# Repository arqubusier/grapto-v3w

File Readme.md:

# Prerequisites

## CAD Development

- Install Freecad
- Install KiCad
- Install Freecad KiCad StepUp plugin.
- install ergogen https://docs.ergogen.xyz/ (see below)
- Install https://github.com/perigoso/keyswitch-kicad-library.
  - Use the "Plugin and Content Manager" program of Kicad.
  - add the library path for Switch_Keyboard_Kailh 
  - Add value of the Kicad variable "KICAD6_3DMODEL_DIR" to secondary 3D folder location in KiCad StepUp
- Download the usb connector 3d model from https://www.molex.com/molex/part/partModels.jsp?&prodLevel=part&partNo=2169900001&channel=products
  to <repo>/grapto-v3w-pcb/216990-0001_stp/
  
### ergogen

$ npm i ergogen
installing globally causes permission errors depending on environment

You need to hack the footprints in gen_src/footprints into your local install of ergogen.

run ergogen (-d flag ouputs svg in addition to svg)

$ cd gen_src
$ ergogen -d config.yaml

Then copy kicad pcbs into the respective kicad project

## FW Development

  # src
  git clone git@github.com:arqubusier/zmk.git

  # packages
  sudo pacman -S git \
    autoconf \
    automake \
    ccache \
    dfu-util \
    libtool \
    make \
    gcc \
    ninja \
    cmake \

  pip install --user west

  # toolchains
  export ZSDK_VERSION=0.13.2
wget -q "https://github.com/zephyrproject-rtos/sdk-ng/releases/download/v${ZSDK_VERSION}/zephyr-toolchain-arm-${ZSDK_VERSION}-linux-x86_64-setup.run" && \
    sh "zephyr-toolchain-arm-${ZSDK_VERSION}-linux-x86_64-setup.run" --quiet -- -d ~/.local/zephyr-sdk-${ZSDK_VERSION} && \
    rm "zephyr-toolchain-arm-${ZSDK_VERSION}-linux-x86_64-setup.run"

  # west setup
  cd <zmk-repo>
  west init -l app/
  west update
  west zephyr-export
  pip install --user -r zephyr/scripts/requirements-base.txt

  yay -S nrf5x-command-line-tools
# FW Development

## Flashing

cd <zmk-repo>
cd app
west flash 
cd 
# FW Development

## Building

west build -p -b grapto_v3w

## Flashing

west flash

# Usage

## Pair on Arch Linux

Set report mode characteristic to report

$ sudo bluetoothctl
menu scan
clean
transport le
back
scan on
connect E9:9E:30:E3:E4:5B

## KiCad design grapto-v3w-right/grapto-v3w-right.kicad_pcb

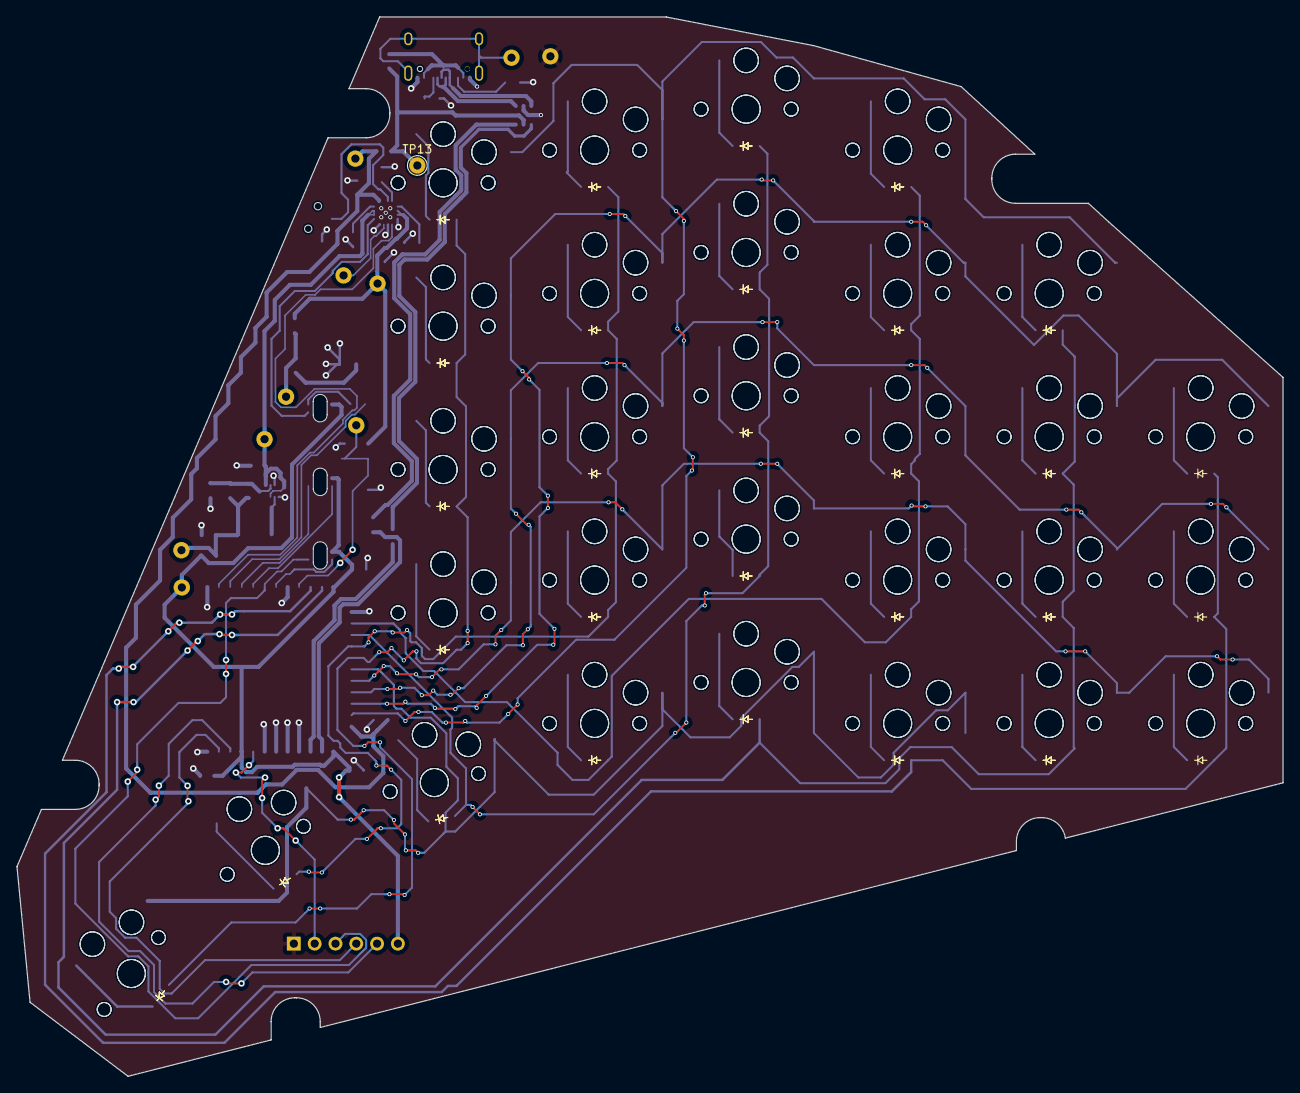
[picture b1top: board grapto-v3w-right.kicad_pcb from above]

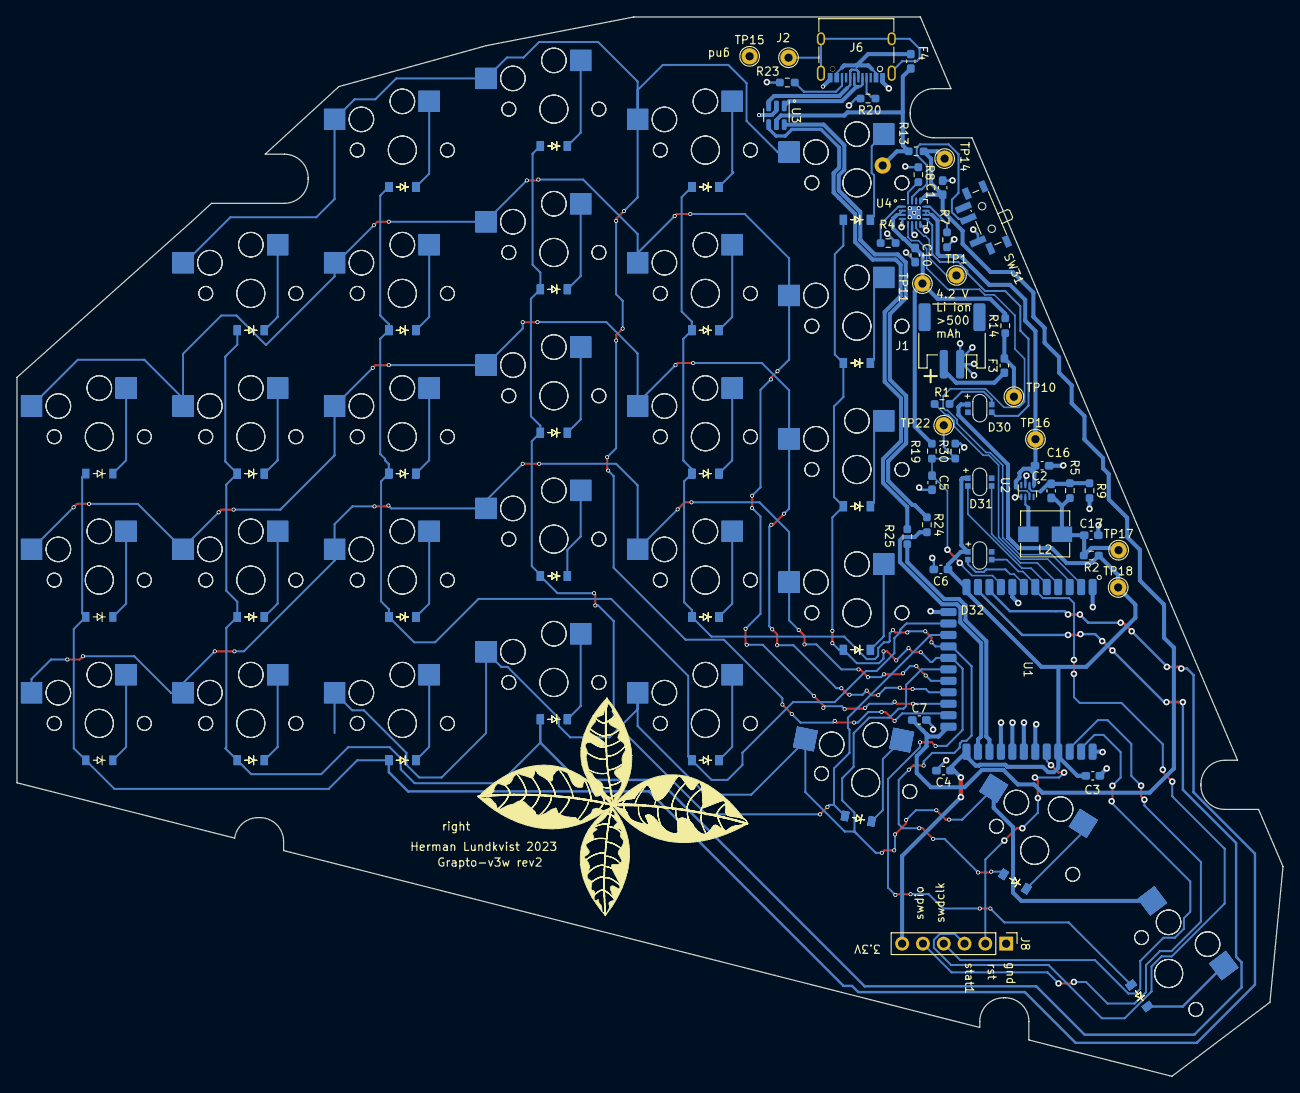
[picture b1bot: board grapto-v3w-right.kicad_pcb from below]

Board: 2 copper layers, 154.6 x 129.3 mm, 163 parts (49 on the bottom side), 78 nets.

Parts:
C1: 1u; C_0603_1608Metric_Pad1.08x0.95mm_HandSolder
C2: 120p; C_0603_1608Metric_Pad1.08x0.95mm_HandSolder
C3, C4, C6, C7, C10, C16, C17: 22u; C_0603_1608Metric_Pad1.08x0.95mm_HandSolder
C5: .1u; C_0603_1608Metric_Pad1.08x0.95mm_HandSolder
D30, D31, D32: LED_ARGB; 23-23B-R6GHBHC-A01-2A
D33, D34, D35, D36, D37, D38, D39, D40, D41, D42, D43, D44, D45, D46, D47, D48, D49, D50, D51, D52, D53, D54, D55, D56, D57, D58, D59, D60, D61, D62, D63, D64, D65, D66, D67, D68, D69, D70, D71, D72, D73, D74, D75, D76, D77, D78, D79, D80, D81, D82, D83, D84, D85, D86, D87: ComboDiode
F3, F4: Polyfuse; Fuse_0603_1608Metric_Pad1.05x0.95mm_HandSolder
J1: Conn_01x02_Female; JST_PH_S2B-PH-SM4-TB_1x02-1MP_P2.00mm_Horizontal
J2: Conn_01x01_Female; TestPoint_THTPad_D2.0mm_Drill1.0mm
J6: USB_C_Receptacle_USB2.0; USB_C_Receptacle_G-Switch_GT-USB-7004
J8: Conn_01x06_Male; PinHeader_1x06_P2.54mm_Vertical
L2: 470n; MHCI05020-R47M-R8
R1: 68; R_0603_1608Metric_Pad0.98x0.95mm_HandSolder
R2, R13, R14: 0.01m; R_0603_1608Metric_Pad0.98x0.95mm_HandSolder
R4: 10K; R_0603_1608Metric_Pad0.98x0.95mm_HandSolder
R5: 453k; R_0603_1608Metric_Pad0.98x0.95mm_HandSolder
R7: 3.3K; R_0603_1608Metric_Pad0.98x0.95mm_HandSolder
R8: 2.2K; R_0603_1608Metric_Pad0.98x0.95mm_HandSolder
R9: 100k; R_0603_1608Metric_Pad0.98x0.95mm_HandSolder
R19: 1M2; R_0603_1608Metric_Pad0.98x0.95mm_HandSolder
R20, R23: 5.1k; R_0603_1608Metric_Pad0.98x0.95mm_HandSolder
R24, R25: 22; R_0603_1608Metric_Pad0.98x0.95mm_HandSolder
R30: 3M; R_0603_1608Metric_Pad0.98x0.95mm_HandSolder
S30, S31, S32, S33, S34, S35, S36, S37, S38, S39, S40, S41, S42, S43, S44, S45, S46, S47, S48, S49, S50, S51, S52, S53, S54, S55, S56, S57, S58, S59, S60, S61, S62, S63, S64, S65, S66, S67, S68, S69, S70, S71, S72, S73, S74, S75, S76, S77, S78, S79, S80, S81, S82, S83, S84, S85, S86, S87: PG1350
SW31: SW_SPDT; SW_SK-3296S-01-L2
TP1, TP10, TP11, TP13, TP14, TP15, TP16, TP17, TP18: TestPoint; TestPoint_THTPad_D2.0mm_Drill1.0mm
TP22: TestPoint_THTPad_D2.0mm_Drill1.0mm
U1: ACN52840
U2: TPS62822DLC; Texas_VSON-HR-8_1.5x2mm_P0.5mm
U3: USBLC6-2SC6; SOT-23-6
U4: BQ24075RGT; VQFN-16-1EP_3x3mm_P0.5mm_EP1.6x1.6mm

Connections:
/controller/BatteryManagement/bat+: F3.1, J1.2
/controller/BatteryManagement/bat_fused: C10.1, R14.2, R19.1, TP11.1, U4.2 (BAT), U4.3 (BAT)
/controller/bat_lvl1: D31.3 (GK), U1.4 (P1.15)
/controller/bat_lvl2: D31.4 (BK), U1.5 (P0.02/AIN0)
/controller/chassi: J2.1, J6.S1 (SHIELD)
/controller/chg_led: D30.3 (GK), U4.9 (~CHG)
/controller/fast_chg: U1.2 (P1.10), U4.5 (EN2)
/controller/fast_chg_led: R1.1, U1.3 (P1.13)
/controller/low_batt: C5.1, R19.2, R30.1, TP22.1, U1.9 (P0.31/AIN7)
/controller/reset: J8.2, U1.31 (RST/SWO)
/controller/status1: D32.3 (GK), J8.3, U1.6 (P0.04/AIN1)
/controller/status2: D32.4 (BK), U1.7 (P0.28/AIN4)
/controller/swdclk: J8.4, U1.34 (SWDCLK)
/controller/swdio: J8.5, U1.33 (SWDIO)
/controller/vdd: C3.1, C4.1, C6.1, D30.1 (A), D31.1 (A), D32.1 (A), J8.6, R2.2, TP18.1, U1.12 (VDD), U1.24 (VDD), U1.32 (VDD)
/controller/vusb: C1.1, C7.1, R13.2, TP14.1, U1.23 (VBUS), U4.13 (IN)
unnamed: C2.1, C17.1, L2.2, R2.1, R5.1, TP17.1
unnamed: D30.2 (RK), R1.2
unnamed: F3.2, R14.1, TP10.1
unnamed: SW31.2 (B), U4.15 (SYSOFF)
unnamed: C2.2, R5.2, R9.1, U2.2 (FB)
unnamed: L2.1, U2.6 (SW)
unnamed: R7.1, U4.12 (ILIM)
unnamed: R8.1, U4.16 (ISET)
unnamed: R4.1, U4.1 (TS)
unnamed: TP1.1, U4.7 (~PGOOD)
USB0_N: R24.1, U3.6 (I/O1)
USB0_P: R25.1, U3.4 (I/O2)
USB_N: R24.2, U1.25 (USB_D-)
USB_P: R25.2, U1.26 (USB_D+)
cc1: J6.A5 (CC1), R20.1
cc2: J6.B5 (CC2), R23.1
col0: D52.2, D53.2, D54.2, D55.2, D58.2, D81.2, D82.2, D83.2, D84.2, D87.2, U1.17 (P0.06)
col0row0: D55.1, D84.1, S55.1, S84.1
col0row1: D54.1, D83.1, S54.1, S83.1
col0row2: D53.1, D82.1, S53.1, S82.1
col0row3: D52.1, D81.1, S52.1, S81.1
col0row4: D58.1, D87.1, S58.1, S87.1
col1: D48.2, D49.2, D50.2, D51.2, D57.2, D77.2, D78.2, D79.2, D80.2, D86.2, U1.16 (P0.27)
col1row0: D51.1, D80.1, S51.1, S80.1
col1row1: D50.1, D79.1, S50.1, S79.1
col1row2: D49.1, D78.1, S49.1, S78.1
col1row3: D48.1, D77.1, S48.1, S77.1
col1row4: D57.1, D86.1, S57.1, S86.1
col2: D43.2, D44.2, D45.2, D46.2, D56.2, D72.2, D73.2, D74.2, D75.2, D85.2, U1.15 (P0.26)
col2row0: D46.1, D75.1, S46.1, S75.1
col2row1: D45.1, D74.1, S45.1, S74.1
col2row2: D44.1, D73.1, S44.1, S73.1
col2row3: D43.1, D72.1, S43.1, S72.1
col2row4: D56.1, D85.1, S56.1, S85.1
col3: D38.2, D39.2, D40.2, D41.2, D47.2, D67.2, D68.2, D69.2, D70.2, D76.2, U1.14 (P0.04/AIN2)
col3row0: D41.1, D70.1, S41.1, S70.1
col3row1: D40.1, D69.1, S40.1, S69.1
col3row2: D39.1, D68.1, S39.1, S68.1
col3row3: D38.1, D67.1, S38.1, S67.1
col3row4: D47.1, D76.1, S47.1, S76.1
col4: D33.2, D34.2, D35.2, D36.2, D42.2, D62.2, D63.2, D64.2, D65.2, D71.2, U1.11 (AIN3)
col4row0: D36.1, D65.1, S36.1, S65.1
col4row1: D35.1, D64.1, S35.1, S64.1
col4row2: D34.1, D63.1, S34.1, S63.1
col4row3: D33.1, D62.1, S33.1, S62.1
col4row4: D42.1, D71.1, S42.1, S71.1
col5: D37.2, D59.2, D60.2, D61.2, D66.2, U1.10 (P0.30/AIN6)
col5row1: D61.1, S32.1, S61.1
col5row2: D60.1, S31.1, S60.1
col5row3: D59.1, S30.1, S59.1
col5row4: D37.1, D66.1, S37.1, S66.1
row0: S36.2, S41.2, S46.2, S51.2, S55.2, S65.2, S70.2, S75.2, S80.2, S84.2, U1.22 (P0.12)
row1: S32.2, S35.2, S40.2, S45.2, S50.2, S54.2, S61.2, S64.2, S69.2, S74.2, S79.2, S83.2, U1.21 (P1.09)
row2: S31.2, S34.2, S39.2, S44.2, S49.2, S53.2, S60.2, S63.2, S68.2, S73.2, S78.2, S82.2, U1.20 (P0.08)
row3: S30.2, S33.2, S38.2, S43.2, S48.2, S52.2, S59.2, S62.2, S67.2, S72.2, S77.2, S81.2, U1.19 (P0.09/NFC1)
row4: S37.2, S42.2, S47.2, S56.2, S57.2, S58.2, S66.2, S71.2, S76.2, S85.2, S86.2, S87.2, U1.18 (P0.10/NFC2)
sysgnd: C1.2, C3.2, C4.2, C5.2, C6.2, C7.2, C10.2, C16.2, C17.2, J1.1, J6.A1 (GND), J6.A12 (GND), J6.B1 (GND), J6.B12 (GND), J8.1, R4.2, R7.2, R8.2, R9.2, R20.2, R23.2, R30.2, SW31.1 (A), TP15.1, U1.1 (GND), U1.8 (P0.29/AIN5), U1.13 (GND), U1.27 (P0.13), U1.28 (P0.15), U1.29 (P0.17), U1.30 (P0.24), U1.35 (GND), U2.3 (AGND), U2.5 (PGND), U3.2 (GND), U4.4 (~CE), U4.6 (EN1), U4.8 (VSS), U4.17 (VSS)
usb1_n: J6.A7 (D-), J6.B7 (D-), U3.1 (I/O1)
usb1_p: J6.A6 (D+), J6.B6 (D+), U3.3 (I/O2)
vbus_fused: F4.2, R13.1, TP13.1, U3.5 (VBUS)
vbus_no_fuse: F4.1, J6.A4 (VBUS), J6.A9 (VBUS), J6.B4 (VBUS), J6.B9 (VBUS)
vsys: C16.1, TP16.1, U2.1 (EN), U2.7 (VIN), U4.10 (OUT), U4.11 (OUT)

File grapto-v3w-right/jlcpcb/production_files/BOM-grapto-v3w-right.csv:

Comment,Designator,Footprint,LCSC
1M2,R19,R_0603_1608Metric_Pad0.98x0.95mm_HandSolder,C137774
.1u,C5,C_0603_1608Metric_Pad1.08x0.95mm_HandSolder,C14663
1u,C1,C_0603_1608Metric_Pad1.08x0.95mm_HandSolder,C15849
0.01m,"R13,R14,R2",R_0603_1608Metric_Pad0.98x0.95mm_HandSolder,C21189
3.3K,R7,R_0603_1608Metric_Pad0.98x0.95mm_HandSolder,C22978
3M,R30,R_0603_1608Metric_Pad0.98x0.95mm_HandSolder,C23156
5.1k,"R20,R23",R_0603_1608Metric_Pad0.98x0.95mm_HandSolder,C23186
22,"R24,R25",R_0603_1608Metric_Pad0.98x0.95mm_HandSolder,C23345
100k,R9,R_0603_1608Metric_Pad0.98x0.95mm_HandSolder,C25803
10K,R4,R_0603_1608Metric_Pad0.98x0.95mm_HandSolder,C25804
453k,R5,R_0603_1608Metric_Pad0.98x0.95mm_HandSolder,C273765
68,R1,R_0603_1608Metric_Pad0.98x0.95mm_HandSolder,C27592
LED_ARGB,"D30,D31,D32",23-23B-R6GHBHC-A01-2A,C2827866
Polyfuse,"F3,F4",Fuse_0603_1608Metric_Pad1.05x0.95mm_HandSolder,C2844463
470n,L2,MHCI05020-R47M-R8,C285730
Conn_01x02_Female,J1,JST_PH_S2B-PH-SM4-TB_1x02-1MP_P2.00mm_Horizontal,C295747
2.2K,R8,R_0603_1608Metric_Pad0.98x0.95mm_HandSolder,C4190
TPS62822DLC,U2,Texas_VSON-HR-8_1.5x2mm_P0.5mm,C473385
SW_SPDT,SW31,SW_SK-3296S-01-L2,C500051
,"S59,S60,S61,S62,S63,S64,S65,S66,S67,S68,S69,S70,S71,S72,S73,S74,S75,S76,S77,S78,S79,S80,S81,S82,S83,S84,S85,S86,S87",PG1350,C5333465
BQ24075RGT,U4,VQFN-16-1EP_3x3mm_P0.5mm_EP1.6x1.6mm,C544783
22u,"C10,C16,C17,C3,C4,C6,C7",C_0603_1608Metric_Pad1.08x0.95mm_HandSolder,C59461
USBLC6-2SC6,U3,SOT-23-6,C7519
,"D59,D60,D61,D62,D63,D64,D65,D66,D67,D68,D69,D70,D71,D72,D73,D74,D75,D76,D77,D78,D79,D80,D81,D82,D83,D84,D85,D86,D87",ComboDiode,C81598
120p,C2,C_0603_1608Metric_Pad1.08x0.95mm_HandSolder,C85974
~,TP22,TestPoint_THTPad_D2.0mm_Drill1.0mm,
TestPoint,TP18,TestPoint_THTPad_D2.0mm_Drill1.0mm,
TestPoint,TP17,TestPoint_THTPad_D2.0mm_Drill1.0mm,
TestPoint,TP16,TestPoint_THTPad_D2.0mm_Drill1.0mm,
TestPoint,TP15,TestPoint_THTPad_D2.0mm_Drill1.0mm,
TestPoint,TP14,TestPoint_THTPad_D2.0mm_Drill1.0mm,
TestPoint,TP13,TestPoint_THTPad_D2.0mm_Drill1.0mm,
TestPoint,TP11,TestPoint_THTPad_D2.0mm_Drill1.0mm,
TestPoint,TP10,TestPoint_THTPad_D2.0mm_Drill1.0mm,
TestPoint,TP1,TestPoint_THTPad_D2.0mm_Drill1.0mm,
ACN52840,U1,ACN52840,
USB_C_Receptacle_USB2.0,J6,USB_C_Receptacle_G-Switch_GT-USB-7004,

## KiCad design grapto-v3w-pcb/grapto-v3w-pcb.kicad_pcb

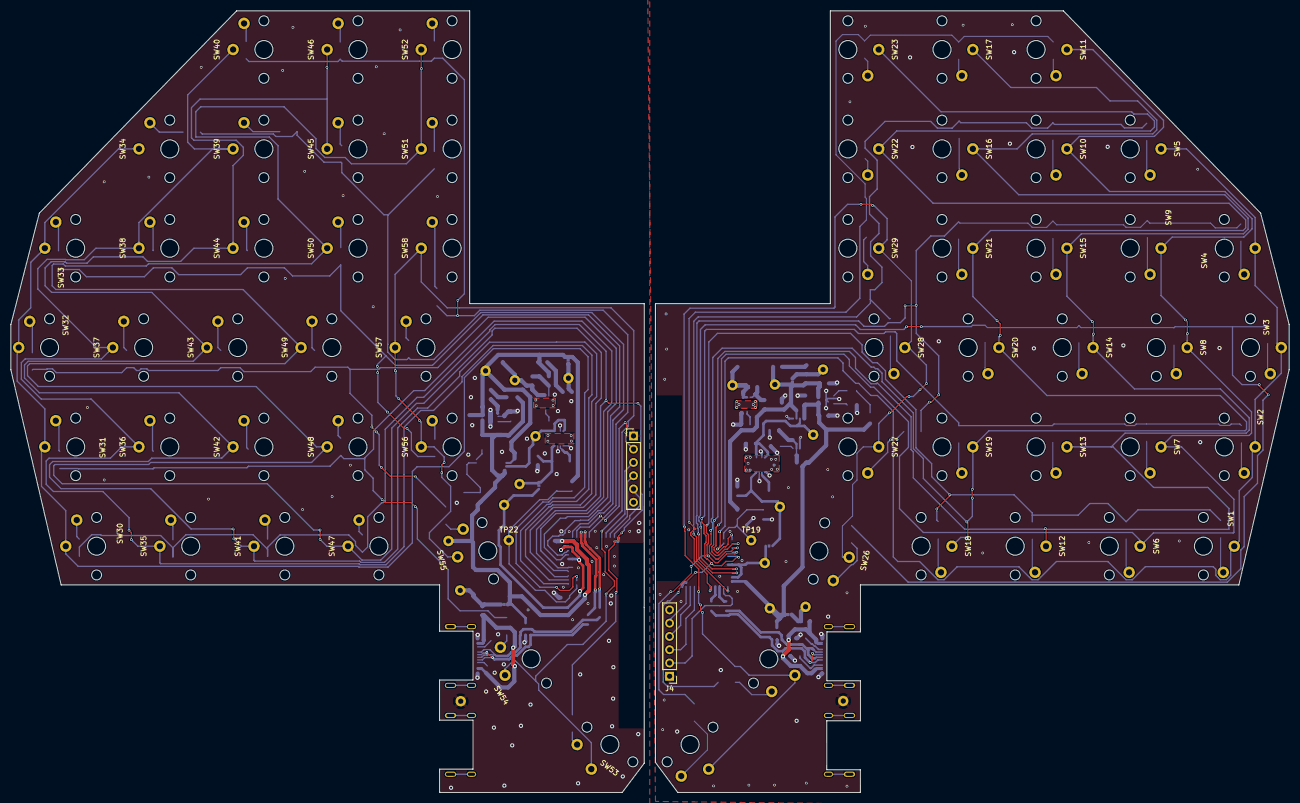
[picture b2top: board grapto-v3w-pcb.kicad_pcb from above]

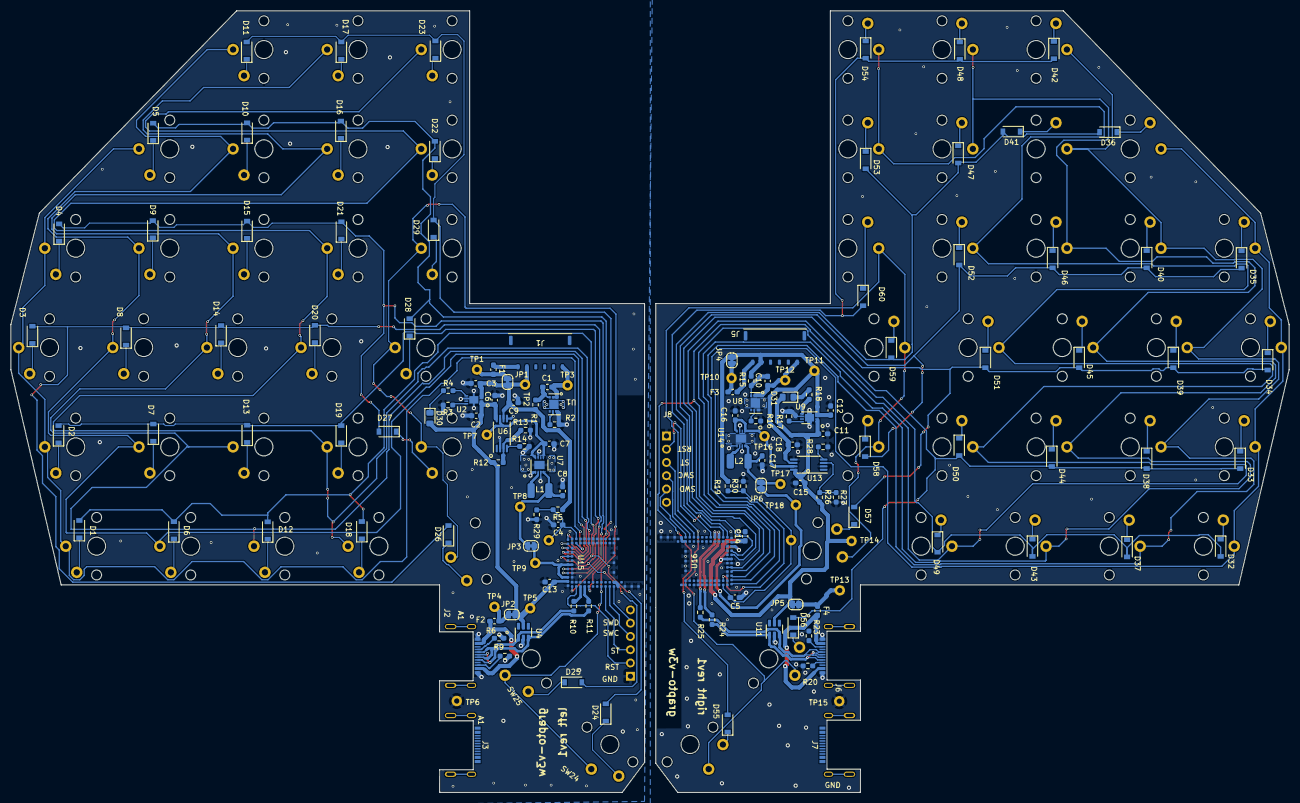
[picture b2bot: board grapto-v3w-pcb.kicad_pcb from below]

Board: 2 copper layers, 244.5 x 149.5 mm, 214 parts (152 on the bottom side), 140 nets.

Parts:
C1, C2, C3, C6, C7, C8, C9, C10, C11, C12, C13, C14, C15, C16, C17, C18: 22u; Fuse_0603_1608Metric_Pad1.05x0.95mm_HandSolder
C4, C5: .1u; C_0603_1608Metric_Pad1.08x0.95mm_HandSolder
D1, D2, D3, D4, D5, D6, D7, D8, D9, D10, D11, D12, D13, D14, D15, D16, D17, D18, D19, D20, D21, D22, D23, D24, D25, D26, D27, D28, D29, D32, D33, D34, D35, D36, D37, D38, D39, D40, D41, D42, D43, D44, D45, D46, D47, D48, D49, D50, D51, D52, D53, D54, D55, D56, D57, D58, D59, D60: D_SOD-123
D30, D31: LED; LED_0805_2012Metric_Pad1.15x1.40mm_HandSolder
F1, F2, F3, F4: Polyfuse; Fuse_0603_1608Metric_Pad1.05x0.95mm_HandSolder
J1, J5: Conn_01x06_Female; df65-6P-1.7V
J2, J3, J6, J7: USB_C_Receptacle_USB2.0; USB_C_Receptacle_molex_2169900001
J4, J8: Conn_01x06_Male; PinHeader_1x06_P2.54mm_Vertical
JP1, JP2, JP3, JP4, JP5, JP6: SolderJumper_2_Bridged; SolderJumper-2_P1.3mm_Bridged_RoundedPad1.0x1.5mm
L1, L2: 2.2; Bourns-SRP0415
R1, R14, R15, R28: 470; R_0603_1608Metric_Pad0.98x0.95mm_HandSolder
R2, R16: 2.7k; R_0603_1608Metric_Pad0.98x0.95mm_HandSolder
R3, R17: 4.7k; R_0603_1608Metric_Pad0.98x0.95mm_HandSolder
R4, R18: 150; R_0603_1608Metric_Pad0.98x0.95mm_HandSolder
R5, R19: 1M; R_0603_1608Metric_Pad0.98x0.95mm_HandSolder
R6, R9, R20, R23: 5.1k; R_0603_1608Metric_Pad0.98x0.95mm_HandSolder
R10, R11, R24, R25: 22; R_0603_1608Metric_Pad0.98x0.95mm_HandSolder
R12, R13, R26, R27: 4.7K; R_0603_1608Metric_Pad0.98x0.95mm_HandSolder
R29, R30: 2M; R_0603_1608Metric_Pad0.98x0.95mm_HandSolder
SW1, SW2, SW3, SW4, SW5, SW6, SW7, SW8, SW9, SW10, SW11, SW12, SW13, SW14, SW15, SW16, SW17, SW18, SW19, SW20, SW21, SW22, SW23, SW24, SW25, SW26, SW27, SW28, SW29, SW30, SW31, SW32, SW33, SW34, SW35, SW36, SW37, SW38, SW39, SW40, SW41, SW42, SW43, SW44, SW45, SW46, SW47, SW48, SW49, SW50, SW51, SW52, SW53, SW54, SW55, SW56, SW57, SW58: SW_Kailh_Choc_V1_1.00u
TP1, TP2, TP3, TP4, TP5, TP6, TP7, TP8, TP9, TP10, TP11, TP12, TP13, TP14, TP15, TP16, TP17, TP18: TestPoint; TestPoint_THTPad_D2.0mm_Drill1.0mm
TP19, TP22: TestPoint_THTPad_D2.0mm_Drill1.0mm
U1, U8: AP9211S-AL; U-DFN2030-6_type_c
U2, U9: MCP7383x-2xMC; DFN-8-1EP_3x2mm_P0.5mm_EP1.75x1.45mm
U4, U11: USBLC6-4SC6; SOT-23-6
U6, U13: TPS2110; TSSOP-8_4.4x3mm_P0.65mm
U7, U14: LM3676SD-3.3; WSON-8-1EP_3x3mm_P0.5mm_EP1.6x2.0mm
U15, U16: Laird_bl653

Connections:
/Left/3.3v: JP6.2 (B), TP18.1, U16.25 (VDD_HV), U16.31 (VDD), U16.32 (SIO_40/SPI_MOSI)
/Left/BatteryManagement/batt+: F3.1, J5.6
/Left/BatteryManagement/batt-: C10.2, J5.1, TP12.1, U8.1 (S1), U8.2 (VSS)
/Left/VBUS_NO_FUSE: F4.1, J6.A4 (VBUS), J6.A9 (VBUS), J6.B4 (VBUS), J6.B9 (VBUS)
/Left/chassi: J6.S1 (SHIELD), U8.7, U14.9 (EP)
/Left/col0: D32.2 (A), D37.2 (A), D43.2 (A), D49.2 (A), D55.2 (A), U16.37 (SIO_07/UART_CTS)
/Left/col1: D33.2 (A), D38.2 (A), D44.2 (A), D50.2 (A), D56.2 (A), U16.35 (SIO_06/UART_TX), U16.36 (SIO_26/I2C_SDA)
/Left/col2: D34.2 (A), D39.2 (A), D45.2 (A), D51.2 (A), D57.2 (A), U16.29 (SIO_08/UART_RX)
/Left/col3: D35.2 (A), D40.2 (A), D46.2 (A), D52.2 (A), D58.2 (A), U16.27 (SIO_11)
/Left/col4: D36.2 (A), D41.2 (A), D47.2 (A), D53.2 (A), D59.2 (A), U16.21 (SIO_16)
/Left/col5: D42.2 (A), D48.2 (A), D54.2 (A), D60.2 (A), U16.13 (SIO_20)
/Left/low_batt: C5.1, R19.2, R30.1, TP22.1, U16.45 (SIO_30/AIN6)
/Left/p+: C12.1, C18.1, J5.5, JP4.2 (B), R15.1, R19.1, TP11.1, U9.3 (VBAT), U9.4 (VBAT), U13.6 (IN2)
/Left/pmux_out: C16.1, TP16.1, U13.7 (OUT), U14.5 (EN), U14.8 (VIN)
/Left/reset: J8.2, U16.19 (nRESET/SIO_18)
/Left/row0: SW30.1, SW31.1, SW32.1, SW33.1, SW34.1, U16.46 (SIO_28/AIN4)
/Left/row1: SW35.1, SW36.1, SW37.1, SW38.1, SW39.1, SW40.1, U16.42 (SIO_01/XL1)
/Left/row2: SW41.1, SW42.1, SW43.1, SW44.1, SW45.1, SW46.1, U16.41 (SIO_01/XL2)
/Left/row3: SW47.1, SW48.1, SW49.1, SW50.1, SW51.1, SW52.1, U16.39 (SIO_05/UART_RTS/AIN3)
/Left/row4: SW53.1, SW54.1, SW55.1, SW56.1, SW57.1, SW58.1, U16.7 (SIO_32)
/Left/status: J8.3, U16.5 (SIO_35/nAutoRUN)
/Left/swdclk: J8.4, U16.3 (SWDCLK)
/Left/swdio: J8.5, U16.1 (SWDIO)
/Left/sysgnd: C5.2, C11.2, C12.2, C14.2, C15.2, C16.2, C17.2, C18.2, J6.A1 (GND), J6.A12 (GND), J6.B1 (GND), J6.B12 (GND), J8.1, R16.2, R17.2, R20.2, R23.2, R27.2, R28.2, R30.2, TP15.1, U8.6 (S2), U9.6 (VSS), U9.9 (EP), U11.2 (GND), U13.2 (D1), U13.5 (GND), U14.1 (PGND), U14.3 (MODE), U14.7 (SGND), U16.0 (GND), U16.2 (SDIO_36), U16.8 (SIO_25), U16.12 (SIO_21), U16.16 (SIO_17), U16.18 (SIO_15), U16.20 (SIO_13), U16.22 (SIO_14), U16.23 (GND), U16.26 (GND), U16.28 (SIO_12), U16.30 (SIO_41/SPI_CLK), U16.33 (GND), U16.34 (SIO_04/AIN2/SPI_MISO), U16.38 (SIO_27/I2C_SCL), U16.40 (GND), U16.43 (GND), U16.44 (SIO_31/AIN7), U16.47 (GND), U16.48 (SIO_29/AIN5), U16.49 (SIO_03/AIN1), U16.50 (SIO_02/AIN0), U16.51 (SIO_46), U16.52 (GND), U16.53 (SIO_47), U16.54 (SIO_44), U16.55 (GND), U16.56 (SIO_45), U16.57 (NFC2/SIO_10), U16.58 (GND), U16.59 (NFC1/SIO_09), U16.62 (SIO_42), U16.63 (SIO_38), U16.64 (SIO_39), U16.65 (GND), U16.66 (GND), U16.67 (GND), U16.68 (GND), U16.69 (GND), U16.70 (GND), U16.71 (GND)
/Left/usb1_n: J6.A7 (D-), J6.B7 (D-), R24.1, U11.1 (I/O1)
/Left/usb1_p: J6.A6 (D+), J6.B6 (D+), R25.1, U11.3 (I/O2)
/Left/vusb: C11.1, C14.1, C15.1, D31.2 (A), JP5.2 (B), R26.1, TP14.1, U9.1 (VDD), U9.2 (VDD), U11.5 (VBUS), U13.8 (IN1), U16.24 (VBUS)
/Right/3.3v: JP3.2 (B), TP9.1, U15.25 (VDD_HV), U15.31 (VDD), U15.32 (SIO_40/SPI_MOSI)
/Right/BatteryManagement/batt+: F1.1, J1.6
/Right/BatteryManagement/batt-: C1.2, J1.1, TP3.1, U1.1 (S1), U1.2 (VSS)
/Right/VBUS_NO_FUSE: F2.1, J2.A4 (VBUS), J2.A9 (VBUS), J2.B4 (VBUS), J2.B9 (VBUS)
/Right/chassi: J2.S1 (SHIELD), U1.7, U7.9 (EP)
/Right/col0: D1.2 (A), D6.2 (A), D12.2 (A), D18.2 (A), D24.2 (A), U15.37 (SIO_07/UART_CTS)
/Right/col1: D2.2 (A), D7.2 (A), D13.2 (A), D19.2 (A), D25.2 (A), U15.35 (SIO_06/UART_TX), U15.36 (SIO_26/I2C_SDA)
/Right/col2: D3.2 (A), D8.2 (A), D14.2 (A), D20.2 (A), D26.2 (A), U15.29 (SIO_08/UART_RX)
/Right/col3: D4.2 (A), D9.2 (A), D15.2 (A), D21.2 (A), D27.2 (A), U15.27 (SIO_11)
/Right/col4: D5.2 (A), D10.2 (A), D16.2 (A), D22.2 (A), D28.2 (A), U15.21 (SIO_16)
/Right/col5: D11.2 (A), D17.2 (A), D23.2 (A), D29.2 (A), U15.13 (SIO_20)
/Right/low_batt: C4.1, R5.2, R29.1, TP19.1, U15.45 (SIO_30/AIN6)
/Right/p+: C3.1, C9.1, J1.5, JP1.2 (B), R1.1, R5.1, TP2.1, U2.3 (VBAT), U2.4 (VBAT), U6.6 (IN2)
/Right/pmux_out: C7.1, TP7.1, U6.7 (OUT), U7.5 (EN), U7.8 (VIN)
/Right/reset: J4.2, U15.19 (nRESET/SIO_18)
/Right/row0: SW1.1, SW2.1, SW3.1, SW4.1, SW5.1, U15.46 (SIO_28/AIN4)
/Right/row1: SW6.1, SW7.1, SW8.1, SW9.1, SW10.1, SW11.1, U15.42 (SIO_01/XL1)
/Right/row2: SW12.1, SW13.1, SW14.1, SW15.1, SW16.1, SW17.1, U15.41 (SIO_01/XL2)
/Right/row3: SW18.1, SW19.1, SW20.1, SW21.1, SW22.1, SW23.1, U15.39 (SIO_05/UART_RTS/AIN3)
/Right/row4: SW24.1, SW25.1, SW26.1, SW27.1, SW28.1, SW29.1, U15.7 (SIO_32)
/Right/status: J4.3, U15.5 (SIO_35/nAutoRUN)
/Right/swdclk: J4.4, U15.3 (SWDCLK)
/Right/swdio: J4.5, U15.1 (SWDIO)
/Right/sysgnd: C2.2, C3.2, C4.2, C6.2, C7.2, C8.2, C9.2, C13.2, J2.A1 (GND), J2.A12 (GND), J2.B1 (GND), J2.B12 (GND), J4.1, R2.2, R3.2, R6.2, R9.2, R13.2, R14.2, R29.2, TP6.1, U1.6 (S2), U2.6 (VSS), U2.9 (EP), U4.2 (GND), U6.2 (D1), U6.5 (GND), U7.1 (PGND), U7.3 (MODE), U7.7 (SGND), U15.0 (GND), U15.2 (SDIO_36), U15.8 (SIO_25), U15.12 (SIO_21), U15.16 (SIO_17), U15.18 (SIO_15), U15.20 (SIO_13), U15.22 (SIO_14), U15.23 (GND), U15.26 (GND), U15.28 (SIO_12), U15.30 (SIO_41/SPI_CLK), U15.33 (GND), U15.34 (SIO_04/AIN2/SPI_MISO), U15.38 (SIO_27/I2C_SCL), U15.40 (GND), U15.43 (GND), U15.44 (SIO_31/AIN7), U15.47 (GND), U15.48 (SIO_29/AIN5), U15.49 (SIO_03/AIN1), U15.50 (SIO_02/AIN0), U15.51 (SIO_46), U15.52 (GND), U15.53 (SIO_47), U15.54 (SIO_44), U15.55 (GND), U15.56 (SIO_45), U15.57 (NFC2/SIO_10), U15.58 (GND), U15.59 (NFC1/SIO_09), U15.62 (SIO_42), U15.63 (SIO_38), U15.64 (SIO_39), U15.65 (GND), U15.66 (GND), U15.67 (GND), U15.68 (GND), U15.69 (GND), U15.70 (GND), U15.71 (GND)
/Right/usb1_n: J2.A7 (D-), J2.B7 (D-), R10.1, U4.1 (I/O1)
/Right/usb1_p: J2.A6 (D+), J2.B6 (D+), R11.1, U4.3 (I/O2)
/Right/vusb: C2.1, C6.1, C13.1, D30.2 (A), JP2.2 (B), R12.1, TP5.1, U2.1 (VDD), U2.2 (VDD), U4.5 (VBUS), U6.8 (IN1), U15.24 (VBUS)
unnamed: C1.1, R1.2, U1.3 (VDD)
unnamed: C8.1, JP3.1 (A), L1.2, TP8.1, U7.4 (FB)
unnamed: C10.1, R15.2, U8.3 (VDD)
unnamed: C17.1, JP6.1 (A), L2.2, TP17.1, U14.4 (FB)
unnamed: D1.1 (K), SW1.2
unnamed: D2.1 (K), SW2.2
unnamed: D3.1 (K), SW3.2
unnamed: D4.1 (K), SW4.2
unnamed: D5.1 (K), SW5.2
unnamed: D6.1 (K), SW6.2
unnamed: D7.1 (K), SW7.2
unnamed: D8.1 (K), SW8.2
unnamed: D9.1 (K), SW9.2
unnamed: D10.1 (K), SW10.2
unnamed: D11.1 (K), SW11.2
unnamed: D12.1 (K), SW12.2
unnamed: D13.1 (K), SW13.2
unnamed: D14.1 (K), SW14.2
unnamed: D15.1 (K), SW15.2
unnamed: D16.1 (K), SW16.2
unnamed: D17.1 (K), SW17.2
unnamed: D18.1 (K), SW18.2
unnamed: D19.1 (K), SW19.2
unnamed: D20.1 (K), SW20.2
unnamed: D21.1 (K), SW21.2
unnamed: D22.1 (K), SW22.2
unnamed: D23.1 (K), SW23.2
unnamed: D24.1 (K), SW24.2
unnamed: D25.1 (K), SW25.2
unnamed: D26.1 (K), SW26.2
unnamed: D27.1 (K), SW27.2
unnamed: D28.1 (K), SW28.2
unnamed: D29.1 (K), SW29.2
unnamed: D30.1 (K), R4.1
unnamed: D31.1 (K), R18.1
unnamed: D32.1 (K), SW30.2
unnamed: D33.1 (K), SW31.2
unnamed: D34.1 (K), SW32.2
unnamed: D35.1 (K), SW33.2
unnamed: D36.1 (K), SW34.2
unnamed: D37.1 (K), SW35.2
unnamed: D38.1 (K), SW36.2
unnamed: D39.1 (K), SW37.2
unnamed: D40.1 (K), SW38.2
unnamed: D41.1 (K), SW39.2
unnamed: D42.1 (K), SW40.2
unnamed: D43.1 (K), SW41.2
unnamed: D44.1 (K), SW42.2
unnamed: D45.1 (K), SW43.2
unnamed: D46.1 (K), SW44.2
unnamed: D47.1 (K), SW45.2
unnamed: D48.1 (K), SW46.2
unnamed: D49.1 (K), SW47.2
unnamed: D50.1 (K), SW48.2
unnamed: D51.1 (K), SW49.2
unnamed: D52.1 (K), SW50.2
unnamed: D53.1 (K), SW51.2
unnamed: D54.1 (K), SW52.2
unnamed: D55.1 (K), SW53.2
unnamed: D56.1 (K), SW54.2
unnamed: D57.1 (K), SW55.2
unnamed: D58.1 (K), SW56.2
unnamed: D59.1 (K), SW57.2
unnamed: D60.1 (K), SW58.2
unnamed: F1.2, JP1.1 (A), TP1.1
unnamed: F2.2, JP2.1 (A), TP4.1
unnamed: F3.2, JP4.1 (A), TP10.1
unnamed: F4.2, JP5.1 (A), TP13.1
unnamed: J2.A5 (CC1), R6.1
unnamed: J2.B5 (CC2), R9.1
unnamed: J6.A5 (CC1), R20.1
unnamed: J6.B5 (CC2), R23.1
unnamed: L1.1, U7.2 (SW)
unnamed: L2.1, U14.2 (SW)
unnamed: R2.1, U1.5 (VM)
unnamed: R3.1, U2.8 (PROG)
unnamed: R4.2, U2.5 (STAT)
unnamed: R12.2, R13.1, U6.3 (VSNS)
unnamed: R14.1, U6.4 (ILIM)
unnamed: R16.1, U8.5 (VM)
unnamed: R17.1, U9.8 (PROG)
unnamed: R18.2, U9.5 (STAT)
unnamed: R26.2, R27.1, U13.3 (VSNS)
unnamed: R28.1, U13.4 (ILIM)
USB_N: R10.2, R24.2, U15.17 (D-), U16.17 (D-)
USB_P: R11.2, R25.2, U15.15 (D+), U16.15 (D+)

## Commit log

2022-03-06 Started with case.
2022-03-06 Added snaps to bottom
2022-03-06 Added snaps
2022-03-19 Found promising snap design.
2022-03-19 improved snaps.
2022-04-03 Updated schematic.
2022-04-04 Added schematic.
2022-04-06 Added requirements
2022-04-09 Before removing pmux.
2022-04-10 minor changes.
2022-04-10 First draft of controller pcb
2022-04-10 Began experimenting with modules
2022-04-10 Think i got modules working.
2022-04-13 Added keymatrix.
2022-04-14 schematic soon finished.
2022-04-18 Footprints done.
2022-04-19 Fixed 3d model paths for pcb.
2022-04-23 Began case rework.
2022-04-23 flipping usbs
2022-04-23 Fixing pcb coordinates.
2022-04-23 Think freecad and kicad models are synced now.
2022-04-23 Reworking case.
2022-04-23 case rework done.
2022-04-24 Ready for layout.
2022-04-24 cleanup.
2022-04-24 Began layout
2022-04-24 layout and snaps
2022-05-06 Added snap supports.
2022-05-11 More layout. esd chip problems.
2022-05-12 all nets connected.
2022-05-14 need to fix silkscreens.
2022-05-15 pcb rev1
2022-05-18 Began changing mcu module.
2022-05-31 Removing fuel gauge. Going for 2-layer board.
2022-06-04 Adjusting schematic to improve layout.
2022-06-04 Left half 2 layer initial layout.
2022-06-05 Initial 2 layer layout right.
2022-06-05 Before drc fixes.
2022-06-06 2-layer layout ready to order.
2022-07-02 Added openocd flashing cfg.
2022-10-06 Bleh.
2022-10-22 Restart case.
2022-12-28 Started with new ergogen based pcb.
2023-02-18 not sure what this is
2023-02-19 Synchronize ergogen output with freecad.
2023-02-19 minor case fix
2023-02-20 Update case to fit how swaps.
2023-02-20 small case tweak.
2023-02-20 update generated pcbs
2023-02-25 Redesign pcb with new mcu and charger
2023-02-26 schematic rewrite draft done.
2023-03-04 Schematic work.
2023-03-05 Schematic fine-tuning.
2023-03-07 Added footprints.
2023-03-08 before adding hotswaps
2023-03-12 left half pcb draft.
2023-03-14 left pcb fix drc.
2023-03-16 Right pcb almost finished.
2023-03-19 Production files sent to jlcpcb.
2023-03-21 Case leds and usb cable cutout.
